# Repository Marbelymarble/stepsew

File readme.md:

# Stepsew

ESP32 firmware for a pedal-controlled sewing-machine stepper motor. Releasing
the pedal after sewing stops the needle at bottom dead center (BDC). Short
pedal taps at rest toggle the needle between BDC and top dead center (TDC).

## Build

```sh
pio run -e esp32dev
```

The project pins Espressif32 7.1.3 and FastAccelStepper 1.3.0. Position capture
uses the classic ESP32's IDF 4 pulse-counter hardware; changing to another ESP32
variant or an IDF 5 platform requires adapting that code. Compiler warnings in
project sources are treated as errors.

## Wiring and configuration

Settings live in [`include/config.h`](include/config.h).

| Signal | GPIO | Configuration |
| --- | --- | --- |
| Motor STEP | 14 | Rising-edge step pulses |
| Motor DIR | 27 | Fixed LOW; forward-only operation |
| Motor ENABLE | 26 | Active LOW |
| Pedal | 2 | 12-bit analog input |
| BDC sensor | 33 | Pull-up input; falling edge marks BDC |

The defaults retain 2,000 pulses per motor revolution, 60–3,000 motor RPM, and
400,000 steps/s² acceleration. Pedal thresholds remain 2,000 for starting and
2,250 for variable speed, with 20 counts of hysteresis. Readings are sampled
every millisecond and averaged over 20 samples. The speed curve uses exponent
1.2 and is clamped to the configured speed limits.

`kStepsPerNeedleCycle` is independent of `kMotorStepsPerRevolution`. The current
value of 4,667 accounts for approximately 2.33 motor revolutions per needle
cycle with 2,000 pulses per motor revolution. Confirm the exact ratio from
pulley tooth counts or the measured BDC crossing interval. This value includes
both the pulley ratio and motor-driver microstep setting.

Align the sensor's falling edge with physical BDC. `kBdcOffsetSteps` can add a
forward offset when the sensor is mounted before BDC. The final position must
remain within the sensor's active LOW region. Homing accepts one captured
sensor pulse to plan the approach; it does not require two crossings with
matching spacing. A fresh edge is then required during the final moving
search. Both homing and the return tap use that same search.

`kBdcToTdcSteps` sets the forward distance from BDC to TDC. Its default is half
a needle cycle (2,333 steps). The return move watches for the next BDC edge
throughout its forward travel from TDC. Both moves rotate
forward. Calibrate this distance if the machine's linkage
does not put TDC exactly half a cycle after BDC. There is no TDC sensor: its
position is inferred from the established BDC reference and counted STEP pulses.

## Short pedal taps

After a successful BDC stop:

- Press and release the pedal within 20–250 ms to raise the needle to TDC.
- Once the needle has stopped at TDC, another short tap lowers it to BDC.
- Hold the pedal for 250 ms to start normal sewing. Releasing it after sewing
  homes to BDC as usual.

The motor stays still while distinguishing a tap from a held press. Tap motion
starts on pedal release. The upward move runs at 60 RPM and takes about
1.2 seconds with the default settings. The downward move scans continuously
at 60 RPM from TDC and requests normal deceleration when a falling edge is
captured. It clears pending capture and the preceding debounce lockout before
starting, and uses speed-dependent debounce throughout the return. Capture is
not restricted to an estimated half-cycle endpoint or a narrow window around it.
The return has a finite travel limit of one nominal needle cycle (4,667 steps),
so a missing signal cannot cause unlimited rotation. It normally stops at the
first usable BDC crossing, about half a cycle from TDC. Homing also allows
a full-cycle search after its approach, so a noisy planning reference cannot
restrict final capture to a narrow predicted window.

Queued pulses and braking cause some travel beyond the captured edge. The
maximum accepted travel beyond the configured BDC offset is calculated from
speed, queue planning, latency allowance, and acceleration
(`kBdcCaptureToleranceSteps`: 44 pulses, about 3.4° of the needle cycle at
60 RPM). A direct scan entered from up to 120 RPM budgets up to 97 pulses
for the initial queued speed and deceleration. This is a limit, not a commanded offset or a guarantee of exact
physical BDC. After motion ends, HIGH samples reset LOW qualification but
allow up to 50 ms (`kBdcStopQualificationMs`) for the mechanism/input to settle
before rejecting the candidate. The sensor must still stay LOW for 10 ms at
rest, followed by final verification. If the sensor's active region is too narrow for braking,
the search continues within its remaining travel budget and otherwise faults.
Align the magnet/sensor and calibrate `kBdcOffsetSteps` for the physical stop.
`BDC stop: edge_to_stop=... offset=...` reports the measured pulse travel.
The next upward move subtracts the measured overrun from its step count to
retain the configured TDC target relative to the captured BDC reference.
Tap duration is measured using the filtered pedal reading
and the existing start/release hysteresis; pulses shorter than 20 ms are ignored.
Adjust `kPedalTapMinMs` and `kPedalTapMaxMs` to change these durations.

Wait for each toggle to finish before tapping again. Short presses during a
toggle are ignored rather than queued. A held press during a toggle resumes
sewing after the same 250 ms threshold, including when the toggle finishes
during that press. A continuous hold cannot trigger repeated toggles.

The controller verifies the final pulse counts and requires a stable LOW BDC
sensor at BDC, or a stable HIGH sensor at TDC, before releasing the motor.
The upward toggle deadline is about 3.3 seconds with the current configuration
and scales with the configured needle-cycle length. Returning to BDC allows
three additional seconds for the search (`kBdcSearchTimeoutMs`). Timeout
messages distinguish motion, sensor search, and final sensor verification.
Failures latch the same fault as
homing; they do not switch the remembered needle position.

Taps are enabled only after a verified BDC stop. At power-up, a pedal press
starts sewing immediately as before; sew and release once to establish the
reference. A detected sensor crossing or changed level while parked invalidates
the reference. After manually moving the handwheel, sew and release again
before using taps: the single BDC sensor cannot detect every manual movement,
particularly near TDC.

## Stop behavior

1. Pedal release starts homing once, from either sewing-speed mode.
2. At or below `kPositionFeedbackMaxRpm` (120 motor RPM by default), release
   converts the existing motion directly into a finite scan at 60 RPM, watching
   for the next Hall edge immediately. Actual, queued, and requested speed
   must all be within the threshold. It logs `Homing: direct low-speed BDC scan`.
   This path has no predicted approach point and requires no earlier reference
   or qualifying stitch. A recent edge still under the sensor can request an
   immediate stop. Travel remains limited to one nominal cycle, and normal
   braking and final LOW verification still apply. An edge already passed
   outside the usable stop region cannot be recovered by reversing.
3. Above the low-speed threshold, the motor changes to 120 RPM
   (4,000 STEP pulses/s). The controller waits
   until current and queued speeds are low enough for 50 ms before planning
   the stop. `kHomingRpm` controls this speed independently of sewing and taps.
4. BDC pulses are tracked during sewing and deceleration for diagnostics.
   Once speed has settled, pending capture and the previous reference are
   discarded. One fresh falling edge at homing speed establishes the reference
   for the approach; no reference from high-speed motion is reused.
5. The motor moves forward to a reachable approach position 93 steps before
   the estimated BDC edge, adding complete needle cycles when required by
   queued pulses and braking distance (`kBdcApproachLeadSteps`). The estimate is
   only an approach target; the final scan allows a full nominal cycle.
   At the current ratio, one needle cycle at homing speed takes about 1.17 s.
6. `Homing: locating the BDC sensor edge` starts the same bounded, continuous
   60 RPM search used by the return tap. A fresh edge with a stable LOW at rest is
   required. An earlier sewing pulse alone cannot establish the final stop.
7. After applying any BDC offset, the controller verifies both the library's
   position and the independent hardware pulse count and requires the sensor
   to remain LOW for 10 ms before releasing the motor outputs.

A pedal press lasting at least 50 ms (`kHomingResumePressMs`) cancels homing
and resumes sewing. Release hysteresis resets that timer; a brief pedal rebound
cannot cancel the stop. The next release either starts a direct low-speed scan
or reacquires a reference at settled speed. A new sewing
session from rest starts fresh reference acquisition, so references from before
a handwheel adjustment are not reused. The controller does not automatically
move or assume it is homed at power-up.

The sensor interrupt applies a speed-dependent falling-edge lockout:

`lockout_us = 1,000,000 × steps_per_needle_cycle / pulses_per_second × 50%`

`kSensorDebouncePercent` controls that fraction. At steady speed the defaults
are about 1,167 ms at 60 motor RPM, 583 ms at 120 RPM, and 23 ms at 3,000 RPM.
The rate uses the highest actual, queued, or requested pulse frequency, so
acceleration shortens the lockout promptly. An active lockout uses the smaller
of its original duration and the current duration: deceleration cannot extend
it and hide the next crossing. Rejected edges do not restart the timer.
Calculations run in the control loop; the ISR uses the published duration and
retains the first edge's timestamp and pulse count.

The moving lockout is bounded by `kSensorDebounceMinUs` (1 ms) and
`kSensorDebounceMaxUs` (2 s). At rest the setting is
`kSensorStoppedDebounceUs` (500 ms). The final BDC search uses the same
speed-dependent debounce as sewing: there is no search-specific 1 ms override.
Candidate rejection does not reset debounce, so repeated edges from the same
burst cannot repeatedly restart braking. A false first edge can still mask a
nearby genuine edge during its lockout; the finite travel and time limits
remain in effect.

This suppresses repeated edges but cannot distinguish an isolated noise spike
from a genuine Hall crossing. No minimum pulse width is required. The handler
does not reread the input level to decide whether an edge counts:
a pulse may already have ended when the interrupt or control loop runs. The
first pending edge's timestamp and hardware pulse count are retained until the
loop consumes them, so bounce cannot replace that reference. Subsequent edges
within three quarters of a needle cycle are ignored based on motor travel.
No exact two-pulse spacing check is used. The final scan searches up to one
nominal cycle from the approach and faults if no usable edge is found. Large raw interrupt counts can indicate
chatter or interference; software cannot establish physical BDC from a signal
that also stays active at unrelated positions.

PCNT unit 7 independently counts STEP pulses, including while the application
is busy. The sensor interrupt captures that count without resetting the
library's position. Unsigned position differences handle counter wraparound.
Units used internally by FastAccelStepper are left available to the library.

`kForwardPlanningMs` is 8 ms, configured only during motor initialization.
FastAccelStepper's task refills roughly every 4 ms; this retains two refill
cycles while reducing queued travel before a normal stop can take effect.
At 60 RPM, 8 ms corresponds to 16 pulses, versus 40 pulses with the former
20 ms setting. Task timing and deceleration add further travel, so this is
neither an exact stop distance nor a guarantee that the magnet remains in the
sensor's active region. Both sewing and positioning use this queue setting;
check smooth high-speed operation as well as the final stop after changing it.

The homing deadline covers two needle cycles at homing speed, maximum
deceleration, settling, a one-second margin, and three seconds for the final
edge search (about 6.6 seconds total with the current settings). Missing or unusable sensor
signals, failed motor commands, and position mismatches latch a fault. The
motor decelerates and its outputs are released once it stops. If a fault stop
has not completed within one second, pending pulses are aborted. Correct the
cause and reset the controller to resume; pressing the pedal cannot clear a
fault. Serial output at 115200 baud reports state transitions and fault causes.

Homing timeout messages identify the stage that failed. They also report the
sensor level, raw falling-edge interrupts, `debounced` edges rejected by the
time lockout, captured/stale/ignored edges,
accepted references, last observed interval, last accepted interval, and
hardware pulse count. The last observed interval may describe rejected bounce;
the accepted interval shows spacing between references used for planning. Counts
cover the current sewing session, including deceleration and reference
acquisition. `raw=0` means no falling-edge interrupts reached the handler;
`raw` can exceed `captured` due to debounce and when multiple admitted edges
arrive before the loop consumes the first one. The interval is diagnostic only, not an exact-spacing
requirement. The 16-bit hardware pulse count wraps every 65,536 steps, while
the library position continues counting; only their low 16 bits must match.
Diagnostics are printed after requesting a stop, so they do not delay capture.

A live `BDC pin=33 HIGH raw=... db=... read=... merged=... us=...` status line
is attempted once per second, including while stopped or faulted. It skips
printing if the serial transmit buffer lacks room. These counters start at boot:

- `raw`: all falling-edge interrupts, before debounce.
- `db`: interrupts rejected by the time lockout.
- `read`: captured events consumed by the control loop, before position filtering.
- `merged`: admitted interrupts coalesced while an earlier event was pending.
- `us`: currently configured lockout in microseconds; an existing lockout may
  be shorter because it began at a faster speed.

The HIGH/LOW value is an instantaneous reading and may miss a short pulse;
the raw counter retains evidence of its interrupt. Moving the magnet past the
sensor by hand while stopped can therefore check capture independently of motor
operation. Search faults also print `observed`, `stale`, `outside`, and
`returned_HIGH` counts. The latter identifies captured candidates rejected
because LOW did not persist at rest. `BDC rejected edges` additionally reports
minimum and maximum pulse travel from those edges to standstill, to help
distinguish signal glitches from braking past the active region. These counts
alone do not prove which cause applies. `outside` includes approach edges before
the final search window, which are normally ignored.

## Hardware verification

A successful build cannot establish mechanical positioning accuracy. Before
using the positioning feature:

- Confirm the driver microstep setting, pulses per needle cycle, rotation
  direction, and the sensor's falling-edge alignment with needle-down BDC.
- Release the pedal from minimum and higher speeds at several points in the
  needle cycle. Confirm the needle consistently finishes at BDC, motion has
  ended before ENABLE is released, and the serial output reaches `Stopped`.
- Press the pedal again while slowing, seeking BDC, and approaching the target.
  Confirm sewing resumes without reversing or briefly disabling the driver.
- After a verified BDC stop, tap once and check physical TDC, then tap again
  and check BDC. The return should report `Tap: locating the BDC sensor edge`
  before `Stopped: needle at BDC`. Confirm each tap produces just one toggle,
  all motion is forward, and the needle stays at its final position after the
  driver is released. Repeat the sequence to check that BDC does not drift.
- Hold the pedal at BDC and TDC. Confirm normal sewing starts after 250 ms and
  releasing the pedal returns to BDC. Check a held press during a toggle too.
- With the mechanism unloaded, check a disconnected sensor and a sensor held
  LOW. Homing must time out, stop the motor, and reject pedal input until reset.
- Check repeated stops and restarting after manually turning the handwheel.
  Release at different points during minimum-speed sewing and check for the
  direct-scan message, without `Homing: approaching BDC`. Release after fast sewing and check for fresh reference
  acquisition after speed settling. If BDC verification fails, check
  the sensor's active region and calibration rather than increasing the timeout.

No software tests are included.

## Source layout

- `main.cpp`: Arduino setup and control-loop scheduling.
- `machine.cpp`: sewing, tap gestures, BDC/TDC positioning, and fault states.
- `stepper.cpp`: FastAccelStepper commands and pulse-based stop planning.
- `bdc_sensor.cpp`: interrupt capture and atomic event transfer.
- `pedal.cpp`: fixed-size averaging and bounded speed mapping.

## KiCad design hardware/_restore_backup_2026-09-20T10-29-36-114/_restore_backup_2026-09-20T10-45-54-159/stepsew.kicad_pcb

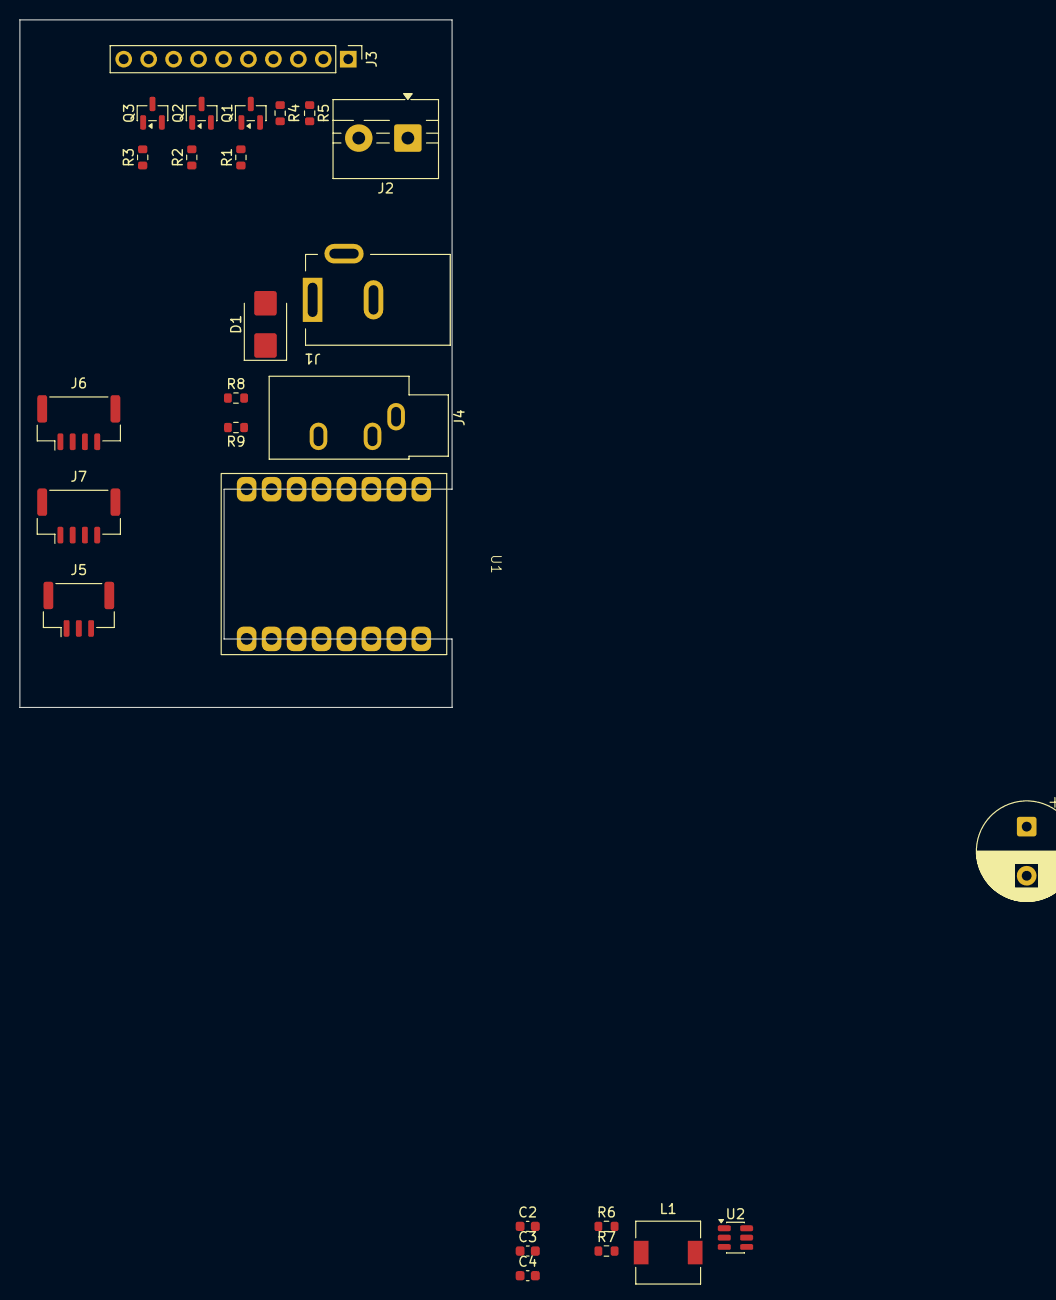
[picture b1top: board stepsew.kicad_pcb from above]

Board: 2 copper layers, 44.0 x 70.0 mm, 27 parts (0 on the bottom side), 27 nets, no tracks yet.

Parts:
C1: 330uF 63V; CP_Radial_D10.0mm_P5.00mm
C2: 2u2; C_0603_1608Metric
C3: 100n; C_0603_1608Metric
C4: 10u; C_0603_1608Metric
D1: D_TVS; D_SMB
J1: Barrel_Jack_MountingPin; BarrelJack_Kycon_KLDX-0202-xC_Horizontal
J2: Servo Power; TerminalBlock_MaiXu_MX126-5.0-02P_1x02_P5.00mm
J3: Servo Header; PinHeader_1x10_P2.54mm_Vertical
J4: Pedal; Jack_3.5mm_CUI_SJ1-3533NG_Horizontal
J5: HallSensor; JST_GH_BM03B-GHS-TBT_1x03-1MP_P1.25mm_Vertical
J6: OLED; JST_GH_BM04B-GHS-TBT_1x04-1MP_P1.25mm_Vertical
J7: Encoder; JST_GH_BM04B-GHS-TBT_1x04-1MP_P1.25mm_Vertical
L1: 15uH; L_6.3x6.3_H3
Q1, Q2, Q3: BC817; SOT-23
R1, R2, R3: 220R; R_0603_1608Metric
R4, R5: 10k; R_0603_1608Metric
R6: 118k; R_0603_1608Metric
R7: 22k1; R_0603_1608Metric
R8: 1k; R_0603_1608Metric
R9: 6k8; R_0603_1608Metric
U1: ESP32-C3-SuperMini
U2: LMR54406; SOT-23-6

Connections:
+3V3: J6.1, R4.2, R5.2, R8.1
+5V: C4.1, J3.6, J3.8, J3.10, J5.1, L1.2, R6.1
+36V: C1.1, C2.1, D1.2 (A2), J1.1, J2.1, U2.4 (~SHDN), U2.5 (VIN)
/Enc_A: J7.1, U1.4 (GPIO4)
/Enc_B: J7.2, U1.3 (GPIO3)
/Enc_SW: J7.3, U1.2 (GPIO2)
/PEDAL: J4.S, R8.2, U1.0 (GPIO0)
/SCL: J6.3, U1.7 (GPIO7)
/SDA: J6.4, U1.6 (GPIO6)
/Sensor: J5.2, U1.1 (GPIO1)
/~ALM: J3.1, R3.1, U1.10 (GPIO10), U1.20 (GPIO20)
/~DIR: R2.1, U1.9 (GPIO9)
/~ENA: R1.1, U1.8 (GPIO8)
/~PED: J3.3, U1.21 (GPIO21)
GND: C1.2, C2.2, C4.2, D1.1 (A1), J1.2, J2.2, J5.3, J6.2, J7.4, Q1.2 (E), Q2.2 (E), Q3.2 (E), R7.2, R9.2, U2.2 (GND)
unnamed: J3.2, R5.1
unnamed: J3.4, R4.1
unnamed: J3.5, Q1.3 (C)
unnamed: J3.7, Q2.3 (C)
unnamed: J3.9, Q3.3 (C)
unnamed: J4.T, R9.1
unnamed: Q1.1 (B), R1.2
unnamed: Q2.1 (B), R2.2
unnamed: Q3.1 (B), R3.2
unnamed: C3.1, U2.1 (CB)
unnamed: R6.2, R7.1, U2.3 (FB)
unnamed: C3.2, L1.1, U2.6 (SW)
